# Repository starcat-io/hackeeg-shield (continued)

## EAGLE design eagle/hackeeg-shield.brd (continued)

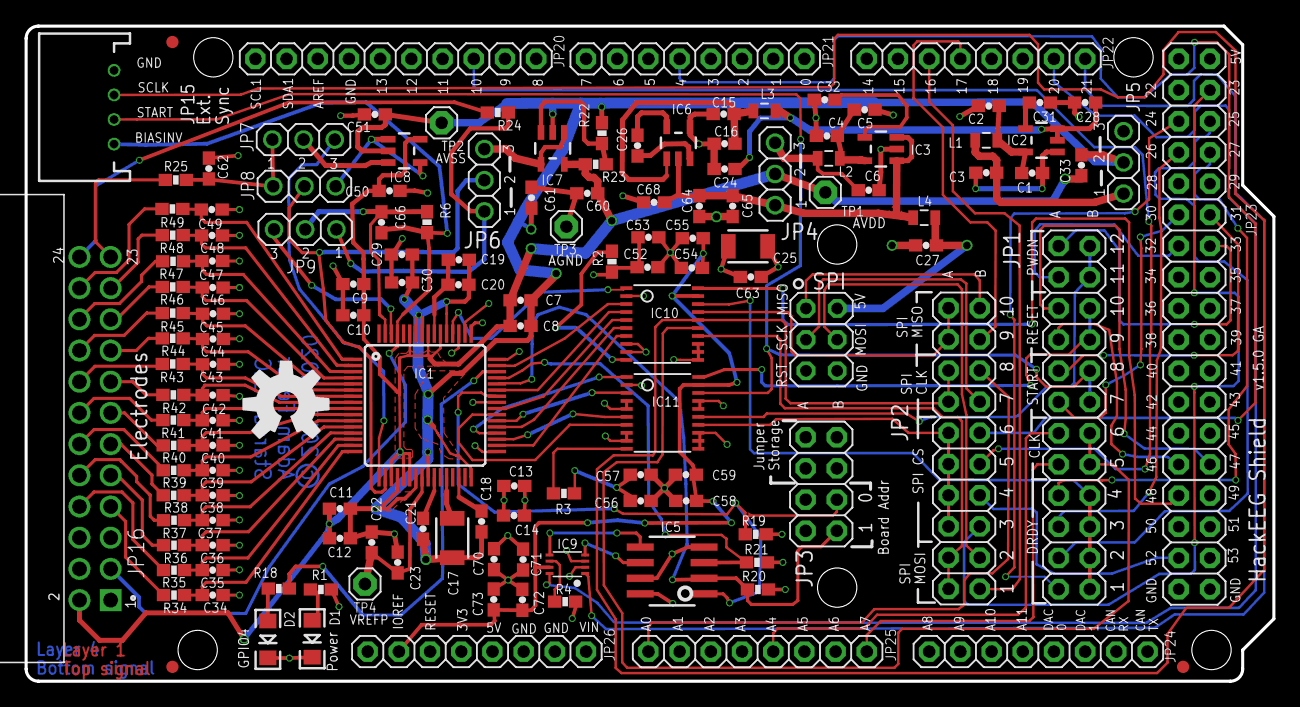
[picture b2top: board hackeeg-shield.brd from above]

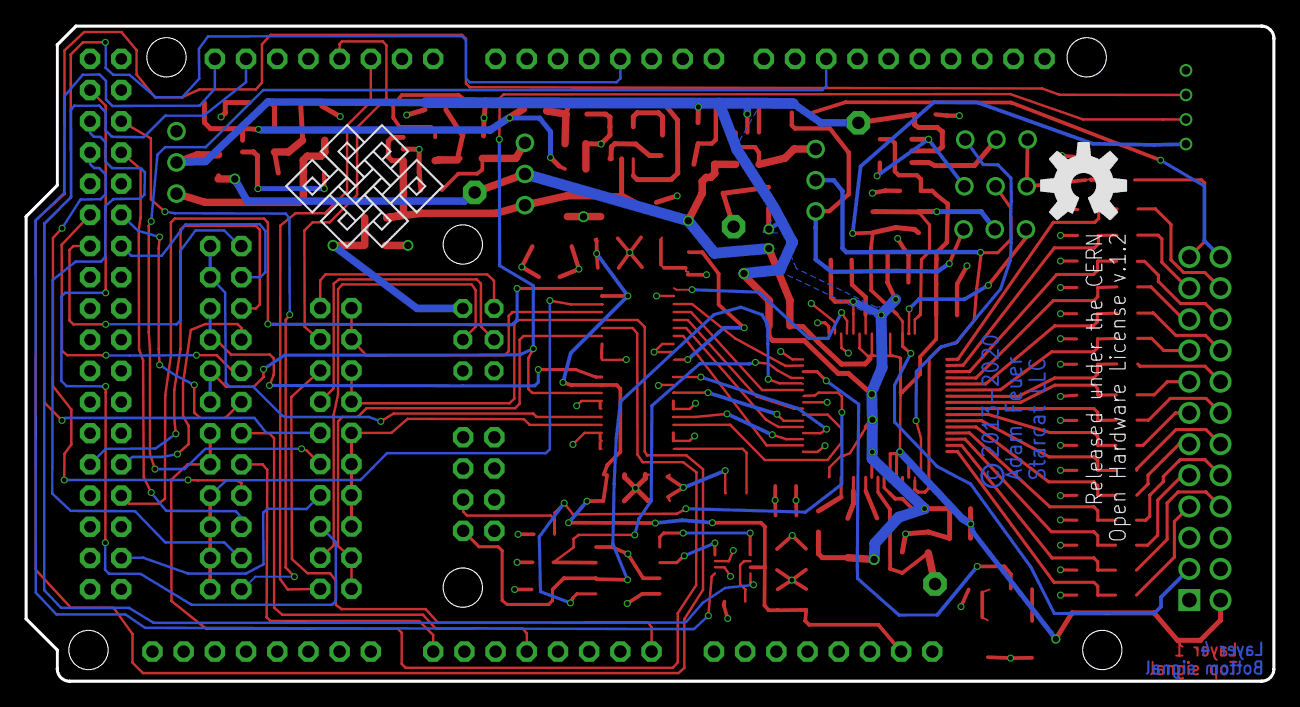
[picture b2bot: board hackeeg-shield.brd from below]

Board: 4 copper layers, 101.6 x 53.3 mm, 145 parts (2 on the bottom side), 122 nets.

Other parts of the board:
U$1, U$4: OSHW-LOGO-L
U$7: ENDLESSKNOT-MEDIUM

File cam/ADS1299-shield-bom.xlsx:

Reference | SMT/TH | Size | Manufacturer | Mfg Part Num | Digikey part number | Quantity1 | Pins | Pins extension | Description | Notes | Quantity2 | Digikey URL
C1,C4,C28 | SMT | 0603 | Samsung Electro-Mechanics America, Inc | CL10A225KP8NNNC | 1276-1085-1-ND | 3 | 2 | 6 | Capacitor - 2.2uF | ?? 3? C15 in twice |  | http://www.digikey.com/product-detail/en/CL10A225KP8NNNC/127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
C17, C25 | SMT | 1210 | Samsung Electro-Mechanics America, Inc | CL32A107MPVNNNE | 1276-3364-1-ND | 2 | 2 | 4 | Capacitor - 100uF |  |  | http://www.digikey.com/product-detail/en/CL32A107MPVNNNE/127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
D1 | SMT | 1206 | Lite-On Inc | LTW-150TK | 160-1737-1-ND | 1 | 2 | 2 | White LED |  |  | http://www.digikey.com/product-detail/en/LTW-150TK/160-1737-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
IC5 | SMT | SOIC-8 | Microchip | 24AA256UID-I/SN | 24AA256UID-I/SN-ND | 1 | 8 | 8 | 24AA256UID-I/SN - SOIC-8 Serial EEPROM |  |  | http://www.digikey.com/product-detail/en/24AA256UID-I%2FSN/2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
IC6 | SMT | SOT23-5 | Texas Instruments | TPS60403DBVT | 296-13418-1-ND | 1 | 5 | 5 | TPS60403DBVT - 60mA Charge Pump Voltage Inverter with Fixed 250kHz Operation |  |  | http://www.digikey.com/product-detail/en/TPS60403DBVT/296-13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
IC2 | SMT | SOT23-5 | Texas Instruments | TPS72325DBVT | 296-15799-1-ND | 1 | 5 | 5 | TPS72325DBVT - Cap-Free, NMOS, 250mA Low Dropout Regulator |  |  | http://www.digikey.com/product-search/en?pv7=2&k=TPS72325DBV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
IC3 | SMT | SOT23-5 | Texas Instruments | TPS73225DBVT | 296-15810-1-ND | 1 | 5 | 5 | TPS73225DBVT - Cap-Free, NMOS, 250mA Low Dropout Regulator |  |  | http://www.digikey.com/product-search/en?pv7=2&k=TPS73225DBV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
U2,U3 | SMT |  | Texas Instruments | TXB0108PWR | 296-21527-1-ND | 2 | 20 | 40 | TXB0108PWR - 8-Bit Bi-Directional Level Shifter |  |  | http://www.digikey.com/product-search/en?pv7=2&k=TXB0108PWR&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
IC9 | SMT | SOT23-5 | Texas Instruments | TXS0102DCTR | 296-21978-1-ND | 1 | 8 | 8 | TXS0102DCTR - 2-Bit Bi-Directional Level Shifter (I2C, etc.) |  |  | http://www.digikey.com/product-detail/en/TXS0102DCTR/296-219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
IC7,IC8 | SMT | SOT23-5 | Texas Instruments | OPA376AIDBVT | 296-21982-1-ND | 2 | 5 | 10 | OPA376AIDBVT - Low-Noise, Low Quiescent Current, Precision Operational Amplifier |  |  | http://www.digikey.com/product-search/en?pv7=2&pv1291=11&k=O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
IC1 | SMT | TQFP64 | Texas Instruments | ADS1299IPAG | 296-34818-1-ND | 1 | 64 | 64 | ADS1299IPAG - 8-Channel, 24-Bit Analog-To-Digital Converter With Integrated EEG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 |  |  | http://www.digikey.com/product-search/en?pv7=2&k=ADS1299IPAG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
C8,C10,C12,C14,C20,C33,C53,C55,C57,C59,C63,C71,C73 | SMT | 0603 | Kemet | C0603C104K8RACTU | 399-1095-1-ND | 13 | 2 | 26 | Capacitor - 0.1uF |  |  | http://www.digikey.com/product-detail/en/C0603C104K8RACTU/39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
C31,C66 | SMT | 0603 | Kemet | C0603C103K8RACTU | 399-11132-1-ND | 2 | 2 | 4 | Capacitor - 0.01uF |  |  | http://www.digikey.com/product-detail/en/C0603C103K8RACTU/39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
C7,C9,C11,C13,C15,C18,C19,C21,C22,C23,C26,C29,C30,C32,C50,C51,C52,C54,C56,C58,C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 | SMT | 0603 | Kemet | C0603C105K8PACTU | 399-3118-1-ND | 25 | 2 | 50 | Capacitor - 1uF |  |  | http://www.digikey.com/product-detail/en/C0603C105K8PACTU/39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
L1,L2,L3,L4 | SMT | 0805 | TDK Corporation | MLZ2012A3R3W | 445-6394-1-ND | 4 | 2 | 8 | Inductors - 3.3 uH |  |  | http://www.digikey.com/product-detail/en/MLF1608A3R3K/445-10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
C2,C3,C5,C16,C64,C6,C24,C27 | SMT | 0603 | TDK Corporation | C1608X5R1A106M080AC | 445-6853-1-ND | 8 | 2 | 16 | Capacitor - 10 uF |  |  | http://www.digikey.com/product-detail/en/C1608X5R1A106M080AC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
J16 | SMT |  | JST Sales America, Inc. | S3B-PH-SM4-TB(LF)(SN) | 455-1750-1-ND | 1 | 2 | 2 | JST_3PIN - PH Series |  |  | http://www.digikey.com/product-search/en?mpart=S3B-PH-K-S%28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
D2 | SMT | 1206 | OSRAM Opto Semiconductors Inc | LH N974-KN-1 | 475-1416-1-ND | 1 | 2 | 2 | Red LED |  |  | http://www.digikey.com/product-detail/en/LH%20N974-KN-1/475-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
C34,C35,C36,C37,C38,C39,C40,C41,C42,C43,C44,C45,C46,C47,C48,C49,C62 | SMT | 0603 | Murata Electronics North America | GRM188R71H472KA01D | 490-1506-1-ND | 17 | 2 | 34 | Capacitor - 4.7nF | 4700pF |  | http://www.digikey.com/product-search/en?pv7=2&k=GRM188R71H4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
JP1 | TH |  | Harwin, Inc. | M20-9981246 | 952-1917-ND | 1 | 24 | 24 | PIN HEADER - CONFIG1 - 2x12 male header |  |  | http://www.digikey.com/product-detail/en/M20-9981246/952-191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
JP0 | TH |  | Harwin, Inc. | M20-9980446 | 952-2123-ND | 1 | 8 | 8 | PIN HEADER - 2x4 male header |  |  | http://www.digikey.com/product-detail/en/M20-9980446/952-212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
JP2 | TH |  | Harwin, Inc. | M20-9981046 | 952-2130-ND | 1 | 20 | 20 | PIN HEADER - 2x10 male header |  |  | http://www.digikey.com/product-detail/en/M20-9981046/952-213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
JP3, JP4, JP5, JP6, JP7 | TH |  | Harwin, Inc. | M20-9990346 | 952-2264-ND | 5 | 3 | 15 | PIN HEADER - 5V-2.5V - 1x3 male header |  |  | http://www.digikey.com/product-detail/en/5-146280-3/5-146280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
R2,R3,R4,R19,R20,R21 | SMT | 0603 | Panasonic Electronic Components | ERJ-3EKF1002V | P10.0KHCT-ND | 6 | 2 | 12 | Resistor - 10k |  |  | http://www.digikey.com/product-detail/en/ERJ-3EKF1002V/P10.0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
R22,R23 | SMT | 0603 | Panasonic Electronic Components | ERJ-3EKF2004V | P2.00MHCT-ND | 2 | 2 | 4 | Resistor - 2M |  |  | http://www.digikey.com/product-detail/en/ERJ-3EKF2004V/P2.00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
R1,R18 | SMT | 0603 | Panasonic Electronic Components | ERJ-3EKF2700V | P270HCT-ND | 2 | 2 | 4 | Resistor - 270 |  |  | http://www.digikey.com/product-detail/en/ERJ-3EKF2700V/P270H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
R6 | SMT | 0603 | Panasonic Electronic Components | ERJ-3EKF2700V | P392HCT-ND | 1 | 2 | 2 | Resistor - 392 |  |  | http://www.digikey.com/product-detail/en/ERJ-3EKF3920V/P392H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
R24,R25,R34,R35,R36,R37,R38,R39,R40,R41,R42,R43,R44,R45,R46,R47,R48,R49 | SMT | 0603 | Panasonic Electronic Components | ERJ-3EKF4991V | P4.99KHCT-ND | 18 | 2 | 36 | Resistor - 4.99k |  |  | http://www.digikey.com/product-detail/en/ERJ-3EKF4991V/P4.99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
J8 | TH |  | Molex | 70247-3051 | WM9827-ND | 1 | 30 | 30 | PIN HEADER - Electrode Connector - 2x15 RA male shrouded header |  |  | http://www.digikey.com/product-detail/en/70247-3051/WM9827-N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
JP9, JP10, JP11, JP12, JP13, JP14 | TH |  | 4UCon | 18689 |  | 6 | 8 | 48 | PIN HEADER - 1x8 female header |  |  | http://www.4uconnector.com/online/SearchPro.asp?FormName=Pro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
JP8 | TH |  | 4UCon | 19950 |  | 1 | 10 | 10 | PIN HEADER - 1x10 female header |  |  | http://www.4uconnector.com/online/SearchPro.asp?FormName=Pro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
JP18 | TH | 0603 | 4UCon | 19950 |  | 1 | 36 | 36 | PIN HEADER - 2x18 female header |  |  | http://www.4uconnector.com/online/SearchPro.asp?FormName=Pro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
SPI | TH |  | 4UCon | 18677 |  | 1 | 6 | 6 | PIN HEADER - SPI |  |  | http://www.4uconnector.com/online/SearchPro.asp?FormName=Pro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
TP1 | NI |  |  |  |  |  |  |  | Pin header 1x1 for 0.1" spacing - AVDD_TEST_POINT | Not installed
TP2 | NI |  |  |  |  |  |  |  | Pin header 1x1 for 0.1" spacing - AVSS_TEST_POINT | Not installed
TP3 | NI |  |  |  |  |  |  |  | Pin header 1x1 for 0.1" spacing - AGND_TEST_POINT | Not installed

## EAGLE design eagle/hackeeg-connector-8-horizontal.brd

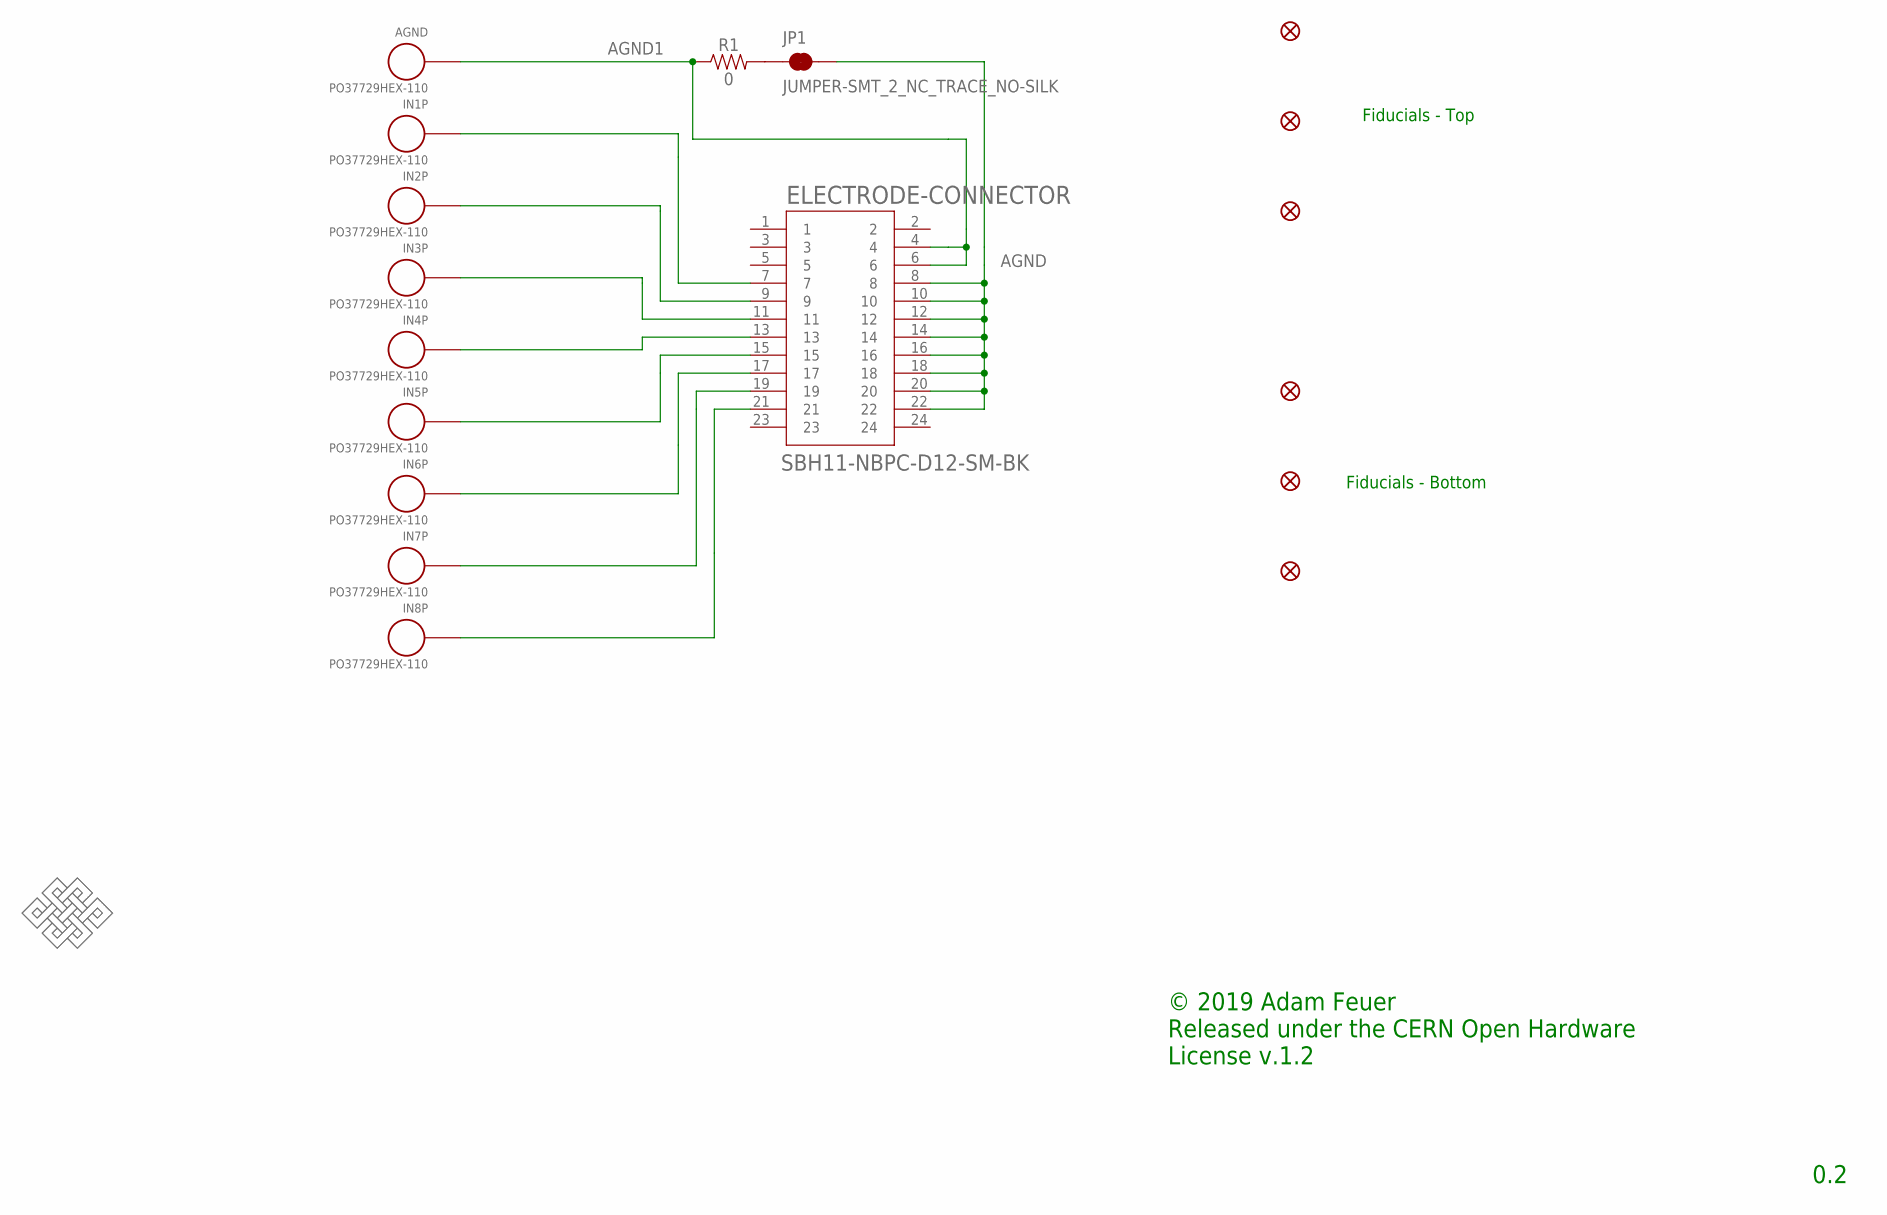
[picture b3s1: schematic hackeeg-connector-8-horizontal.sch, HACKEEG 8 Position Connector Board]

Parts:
AGND: PO37729HEX-110; HEX-110
ELECTRODE-CONNECTOR: SBH11-NBPC-D12-SM-BK; SULLINS_SBH11-NBPC-D12-SM-BK
FD1, FD2, FD3, FD4, FD5, FD6: FIDUCIAL1X2; FIDUCIAL-1X2
IN1P, IN2P, IN3P, IN4P, IN5P, IN6P, IN7P, IN8P: PO37729HEX-110; HEX-110
JP1: JUMPER-SMT_2_NC_TRACE_NO-SILK; SMT-JUMPER_2_NC_TRACE_NO-SILK
R1: 0; 0603
U$1: ENDLESSKNOTENDLESSKNOT-MEDIUM; ENDLESSKNOT-MEDIUM

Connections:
AGND: ELECTRODE-CONNECTOR.8, ELECTRODE-CONNECTOR.10, ELECTRODE-CONNECTOR.12, ELECTRODE-CONNECTOR.14, ELECTRODE-CONNECTOR.16, ELECTRODE-CONNECTOR.18, ELECTRODE-CONNECTOR.20, ELECTRODE-CONNECTOR.22, JP1.2
AGND1: AGND.SIGNAL, ELECTRODE-CONNECTOR.4, ELECTRODE-CONNECTOR.6, R1.1
unnamed: ELECTRODE-CONNECTOR.7, IN1P.SIGNAL
unnamed: ELECTRODE-CONNECTOR.9, IN2P.SIGNAL
unnamed: ELECTRODE-CONNECTOR.11, IN3P.SIGNAL
unnamed: ELECTRODE-CONNECTOR.13, IN4P.SIGNAL
unnamed: ELECTRODE-CONNECTOR.15, IN5P.SIGNAL
unnamed: ELECTRODE-CONNECTOR.17, IN6P.SIGNAL
unnamed: ELECTRODE-CONNECTOR.19, IN7P.SIGNAL
unnamed: ELECTRODE-CONNECTOR.21, IN8P.SIGNAL
unnamed: JP1.1, R1.2

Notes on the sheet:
Fiducials - Top
Fiducials - Bottom
© 2019 Adam Feuer Released under the CERN Open Hardware License v.1.2
0.2

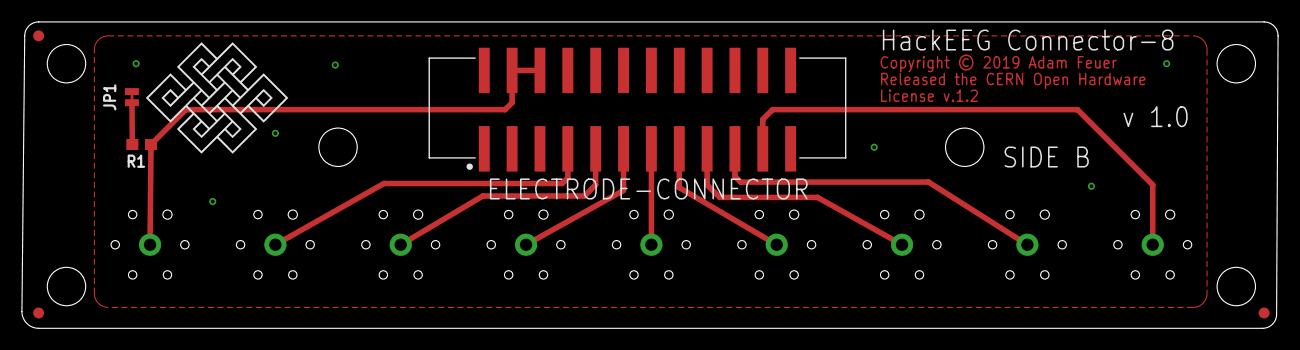
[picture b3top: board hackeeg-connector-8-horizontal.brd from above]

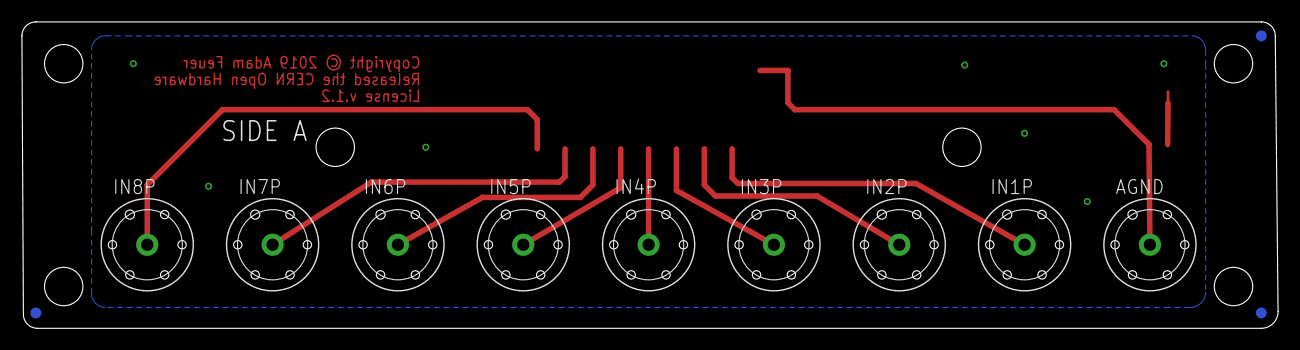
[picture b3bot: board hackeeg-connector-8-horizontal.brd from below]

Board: 2 copper layers, 114.6 x 27.9 mm, 19 parts (12 on the bottom side), 11 nets.

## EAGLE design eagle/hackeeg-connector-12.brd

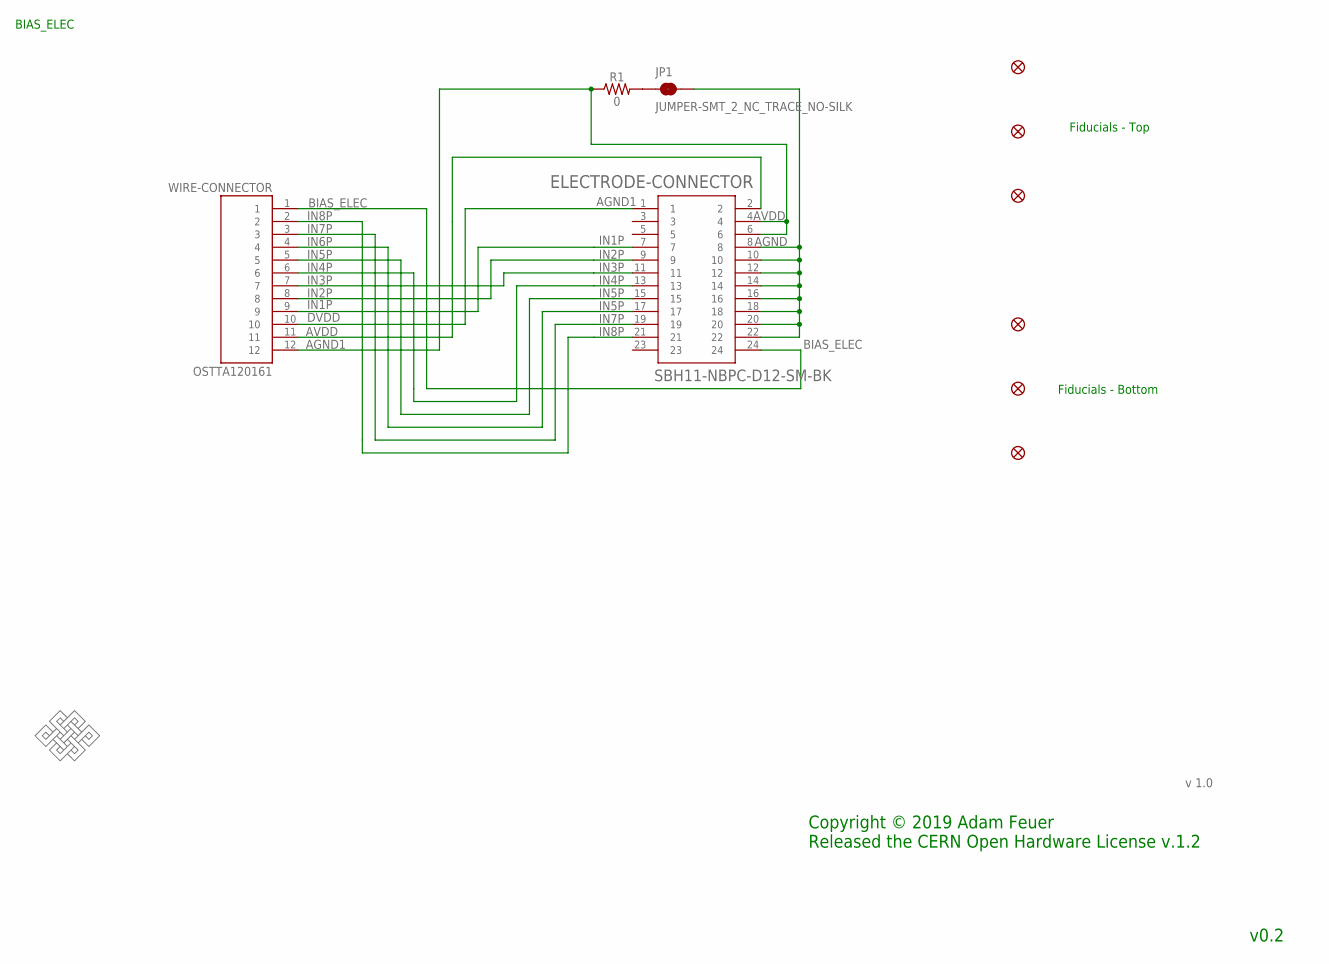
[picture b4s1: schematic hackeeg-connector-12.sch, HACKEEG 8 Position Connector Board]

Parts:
ELECTRODE-CONNECTOR: SBH11-NBPC-D12-SM-BK; SULLINS_SBH11-NBPC-D12-SM-BK
FD1, FD2, FD3, FD4, FD5, FD6: FIDUCIAL1X2; FIDUCIAL-1X2
JP1: JUMPER-SMT_2_NC_TRACE_NO-SILK; SMT-JUMPER_2_NC_TRACE_NO-SILK
R1: 0; 0603
U$1: ENDLESSKNOTENDLESSKNOT-MEDIUM; ENDLESSKNOT-MEDIUM
WIRE-CONNECTOR: OSTTA120161; ONSHORE_OSTTA120161

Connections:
AGND: ELECTRODE-CONNECTOR.8, ELECTRODE-CONNECTOR.10, ELECTRODE-CONNECTOR.12, ELECTRODE-CONNECTOR.14, ELECTRODE-CONNECTOR.16, ELECTRODE-CONNECTOR.18, ELECTRODE-CONNECTOR.20, ELECTRODE-CONNECTOR.22, JP1.2
AGND1: ELECTRODE-CONNECTOR.4, ELECTRODE-CONNECTOR.6, R1.1, WIRE-CONNECTOR.12
AVDD: ELECTRODE-CONNECTOR.2, WIRE-CONNECTOR.11
BIAS_ELEC: ELECTRODE-CONNECTOR.24, WIRE-CONNECTOR.1
DVDD: ELECTRODE-CONNECTOR.1, WIRE-CONNECTOR.10
IN1P: ELECTRODE-CONNECTOR.7, WIRE-CONNECTOR.9
IN2P: ELECTRODE-CONNECTOR.9, WIRE-CONNECTOR.8
IN3P: ELECTRODE-CONNECTOR.11, WIRE-CONNECTOR.7
IN4P: ELECTRODE-CONNECTOR.13, WIRE-CONNECTOR.6
IN5P: ELECTRODE-CONNECTOR.15, WIRE-CONNECTOR.5
IN6P: ELECTRODE-CONNECTOR.17, WIRE-CONNECTOR.4
IN7P: ELECTRODE-CONNECTOR.19, WIRE-CONNECTOR.3
IN8P: ELECTRODE-CONNECTOR.21, WIRE-CONNECTOR.2
unnamed: JP1.1, R1.2

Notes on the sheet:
Fiducials - Top
Fiducials - Bottom
BIAS_ELEC
IN1P
IN2P
IN3P
IN4P
IN5P
IN7P
IN8P
AGND1
AVDD
v 1.0
v0.2
Copyright © 2019 Adam Feuer Released the CERN Open Hardware License v.1.2

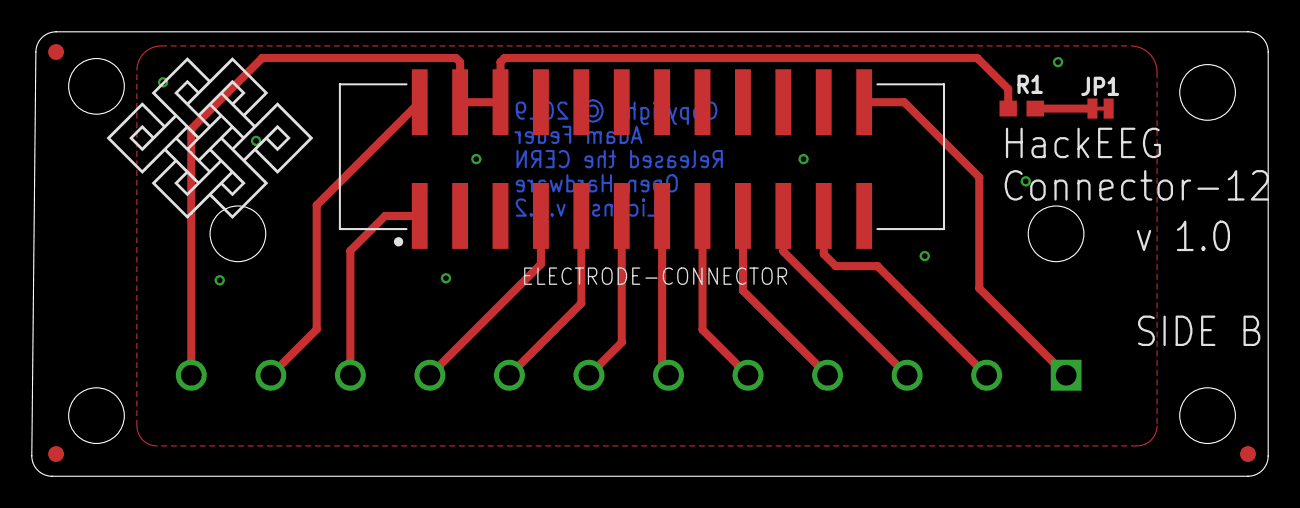
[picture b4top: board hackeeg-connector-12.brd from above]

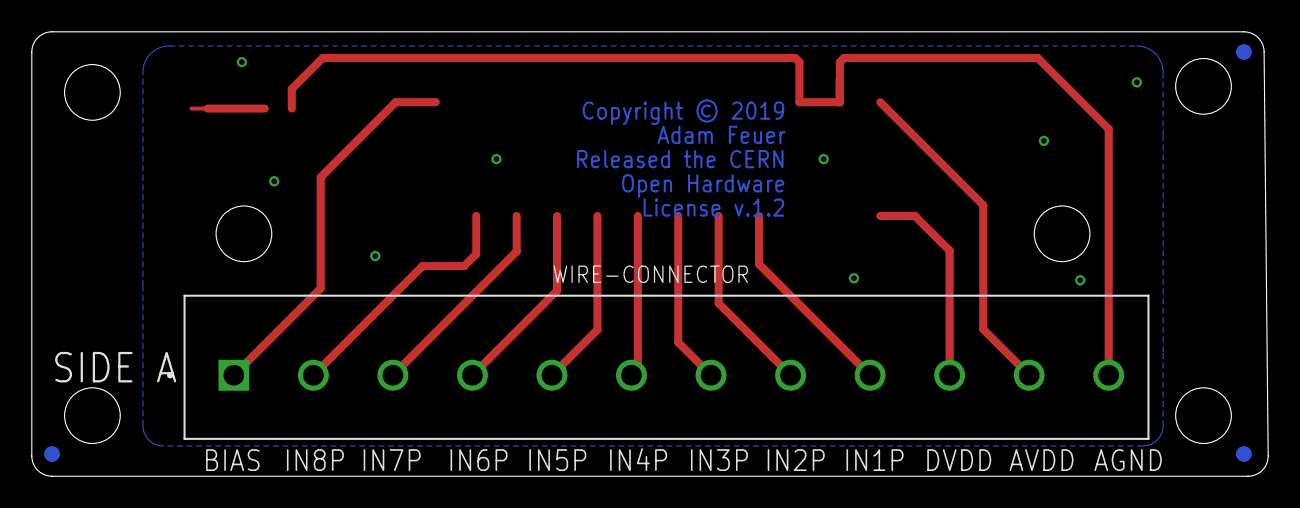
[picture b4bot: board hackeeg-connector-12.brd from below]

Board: 2 copper layers, 77.7 x 27.9 mm, 11 parts (4 on the bottom side), 14 nets.

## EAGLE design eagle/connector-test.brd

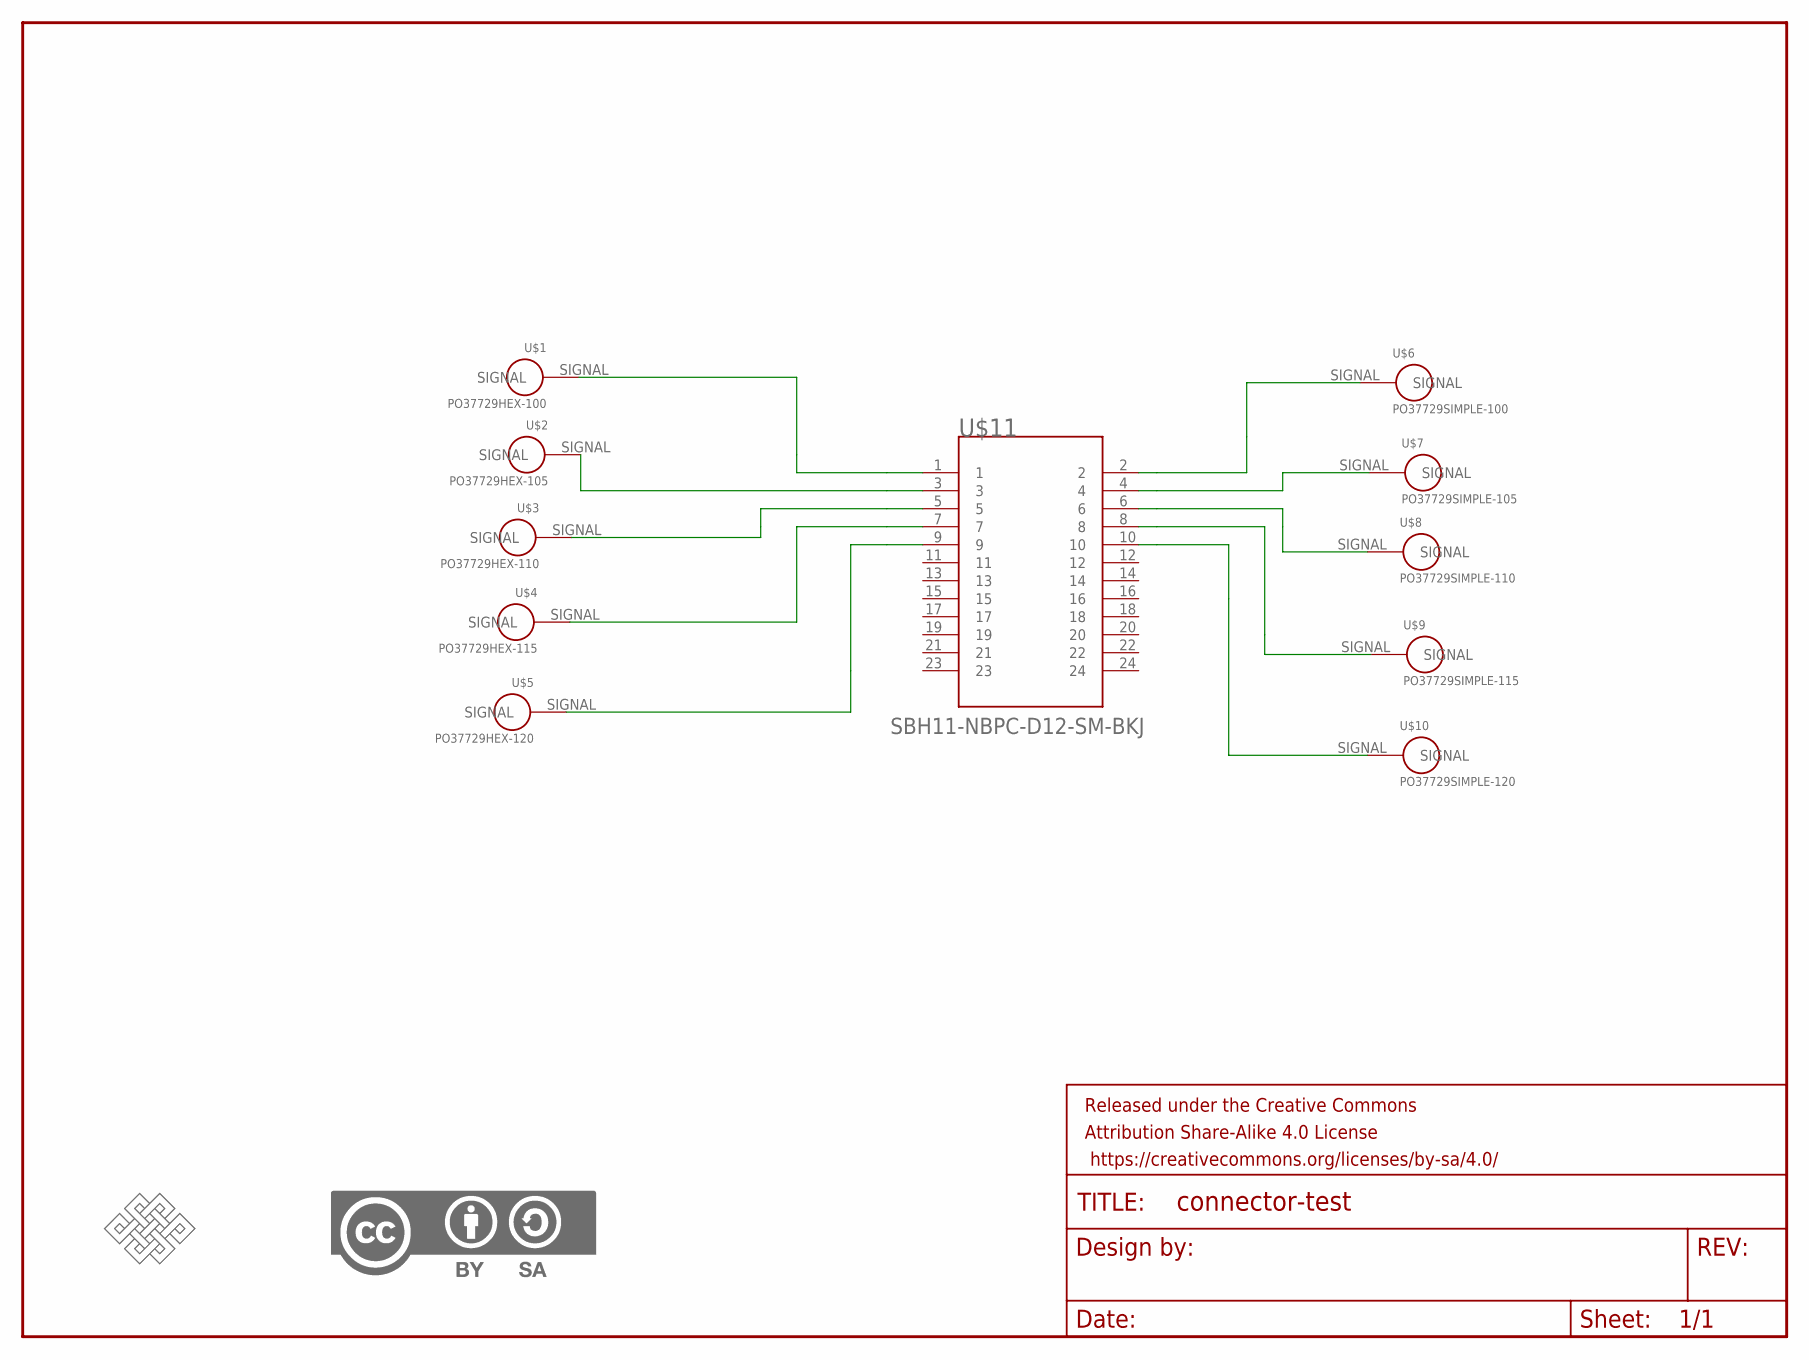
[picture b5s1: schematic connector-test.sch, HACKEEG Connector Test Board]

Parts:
FRAME1: FRAME-LETTER; CREATIVE_COMMONS
U$1: PO37729HEX-100; HEX-100
U$2: PO37729HEX-105; HEX-105
U$3: PO37729HEX-110; HEX-110
U$4: PO37729HEX-115; HEX-115
U$5: PO37729HEX-120; HEX-120
U$6: PO37729SIMPLE-100; SIMPLE-100
U$7: PO37729SIMPLE-105; SIMPLE-105
U$8: PO37729SIMPLE-110; SIMPLE-110
U$9: PO37729SIMPLE-115; SIMPLE-115
U$10: PO37729SIMPLE-120; SIMPLE-120
U$11: SBH11-NBPC-D12-SM-BKJ; SBH11-NBPC-D12-SM-BK
U$12: ENDLESSKNOTENDLESSKNOT-LARGE; ENDLESSKNOT
U$13: CC-BY-SA

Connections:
unnamed: U$1.SIGNAL, U$11.1
unnamed: U$2.SIGNAL, U$11.3
unnamed: U$3.SIGNAL, U$11.5
unnamed: U$4.SIGNAL, U$11.7
unnamed: U$5.SIGNAL, U$11.9
unnamed: U$6.SIGNAL, U$11.2
unnamed: U$7.SIGNAL, U$11.4
unnamed: U$8.SIGNAL, U$11.6
unnamed: U$9.SIGNAL, U$11.8
unnamed: U$10.SIGNAL, U$11.10

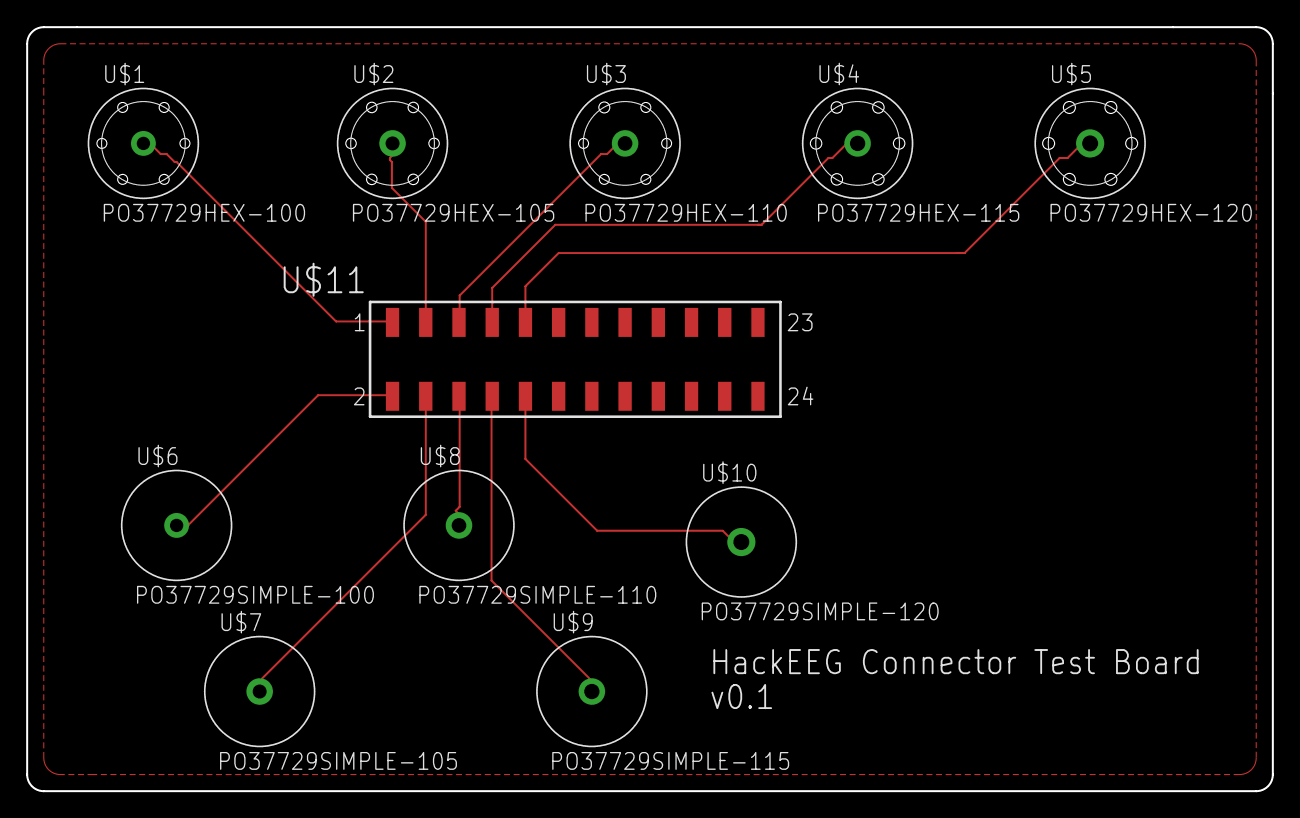
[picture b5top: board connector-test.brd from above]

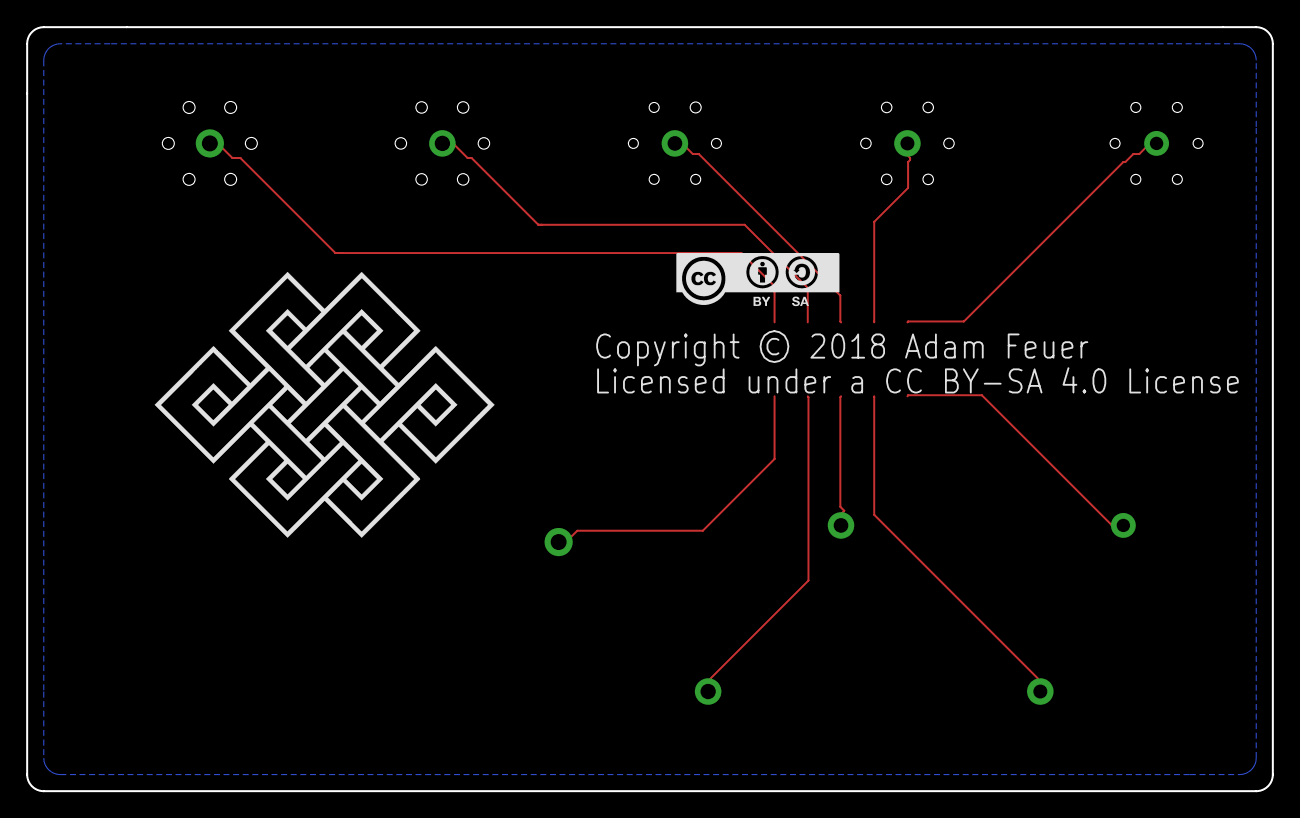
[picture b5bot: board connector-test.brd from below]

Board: 2 copper layers, 95.2 x 58.4 mm, 14 parts (2 on the bottom side), 10 nets.
